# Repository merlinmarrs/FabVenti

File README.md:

# FabVenti
Stepper Motor Driver with Atmega328p and DRV8833
Developed by Fab Lab Digiscope

See PDF for assembly instructions

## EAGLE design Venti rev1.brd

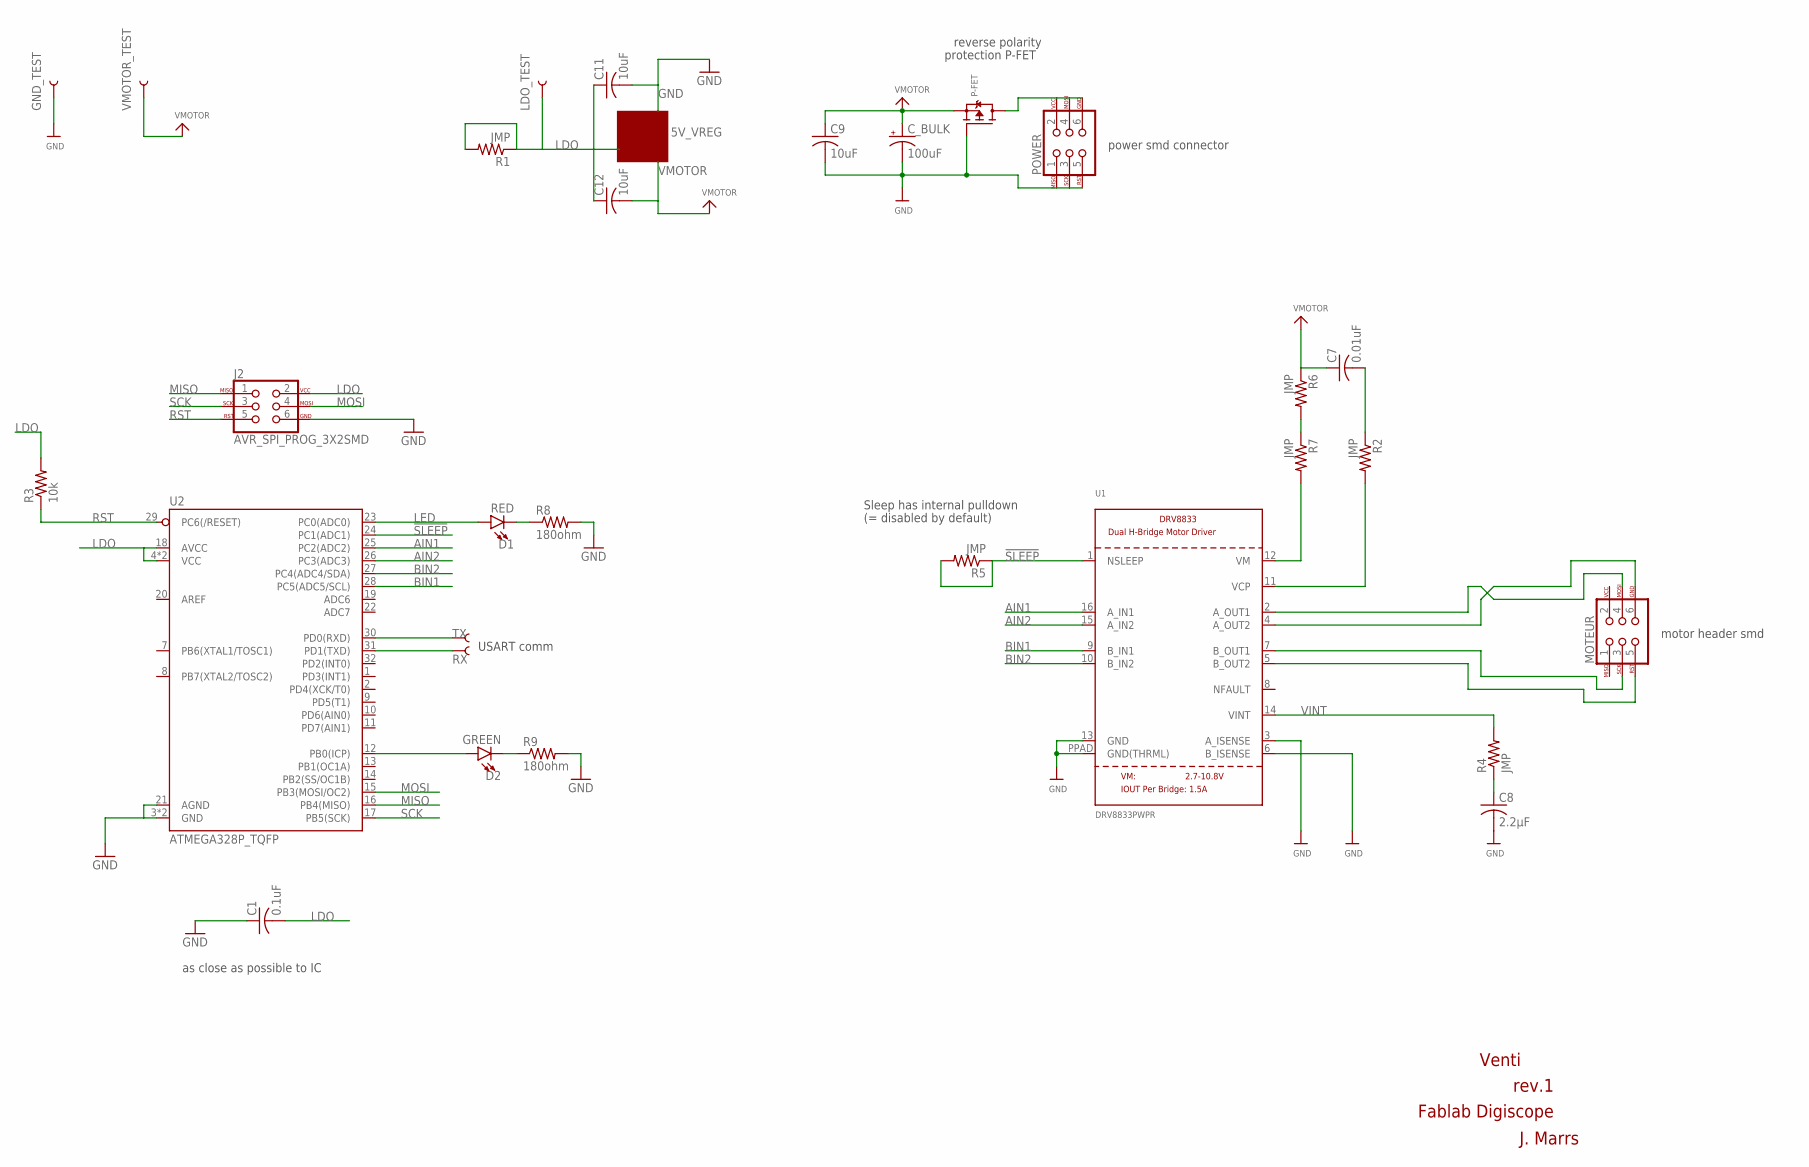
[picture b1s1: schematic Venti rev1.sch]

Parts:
5V_VREG: MOSFET_PCH-DMG2305UX-7; SOT23-3
C1: 0.1uF; C1206
C7: 0.01uF; C1206
C8: 2.2μF; C1206
C9, C11, C12: 10uF; C1206
C_BULK: 100uF; CPOL-RADIAL-2.5MM-6.5MM
D1: RED; LED-1206
D2: GREEN; LED-1206
GND_TEST: TEST-POINT3; PAD.03X.03
J2: AVR_SPI_PROG_3X2SMD; 2X3_SMT_POSTS
LDO_TEST: TEST-POINT3; PAD.03X.03
MOTEUR: AVR_SPI_PROG_3X2SMD; 2X3_SMT_POSTS
P-FET: MOSFET-PWIDE; SOT23-WIDE
POWER: AVR_SPI_PROG_3X2SMD; 2X3_SMT_POSTS
R1, R2, R4, R5, R6, R7: JMP; R1206
R3: 10k; R1206
R8, R9: 180ohm; R1206
RX: TEST-POINT3; PAD.03X.03
TX: TEST-POINT3; PAD.03X.03
U1: DRV8833PWPR; HTSSOP16
U2: ATMEGA328P_TQFP; TQFP32-08
VMOTOR_TEST: TEST-POINT3; PAD.03X.03

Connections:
!SLEEP: R5.1, R5.2, U1.1 (NSLEEP), U2.24 (PC1(ADC1))
AIN1: U1.16 (A_IN1), U2.25 (PC2(ADC2))
AIN2: U1.15 (A_IN2), U2.26 (PC3(ADC3))
AOUT1: MOTEUR.4, U1.2 (A_OUT1)
AOUT2: MOTEUR.6, U1.4 (A_OUT2)
BIN1: U1.9 (B_IN1), U2.28 (PC5(ADC5/SCL))
BIN2: U1.10 (B_IN2), U2.27 (PC4(ADC4/SDA))
BOUT1: MOTEUR.3, U1.7 (B_OUT1)
BOUT2: MOTEUR.5, U1.5 (B_OUT2)
GND: 5V_VREG.3 (D), C1.1, C8.2, C9.2, C11.2, C_BULK.2 (-), GND_TEST.P$1, J2.6, P-FET.1 (G), POWER.1, POWER.3, POWER.5, R8.2, R9.2, U1.3 (A_ISENSE), U1.6 (B_ISENSE), U1.13 (GND), U1.PPAD (GND(THRML)), U2.3 (GND), U2.5 (GND), U2.21 (AGND)
LDO: 5V_VREG.1 (G), C1.2, C11.1, C12.1, J2.2, LDO_TEST.P$1, R1.1, R1.2, R3.2, U2.4 (VCC), U2.6 (VCC), U2.18 (AVCC)
LED: D1.A, U2.23 (PC0(ADC0))
MISO: J2.1, U2.16 (PB4(MISO))
MOSI: J2.4, U2.15 (PB3(MOSI/OC2))
unnamed: C8.1, R4.1
unnamed: C7.2, R2.1
unnamed: R7.2, U1.12 (VM)
unnamed: R6.2, R7.1
unnamed: TX.P$1, U2.30 (PD0(RXD))
unnamed: RX.P$1, U2.31 (PD1(TXD))
unnamed: R2.2, U1.11 (VCP)
unnamed: D2.A, U2.12 (PB0(ICP))
unnamed: D1.C, R8.1
unnamed: D2.C, R9.1
PWRIN: P-FET.3 (D), POWER.2, POWER.4, POWER.6
RST: J2.5, R3.1, U2.29 (PC6(/RESET))
SCK: J2.3, U2.17 (PB5(SCK))
VINT: R4.2, U1.14 (VINT)
VMOTOR: 5V_VREG.2 (S), C7.1, C9.1, C12.2, C_BULK.1 (+), P-FET.2 (S), R6.1, VMOTOR_TEST.P$1

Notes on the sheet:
Sleep has internal pulldown
(= disabled by default)
motor header smd
power smd connector
Venti
rev.1
Fablab Digiscope
J. Marrs
USART comm
as close as possible to IC
reverse polarity
protection P-FET

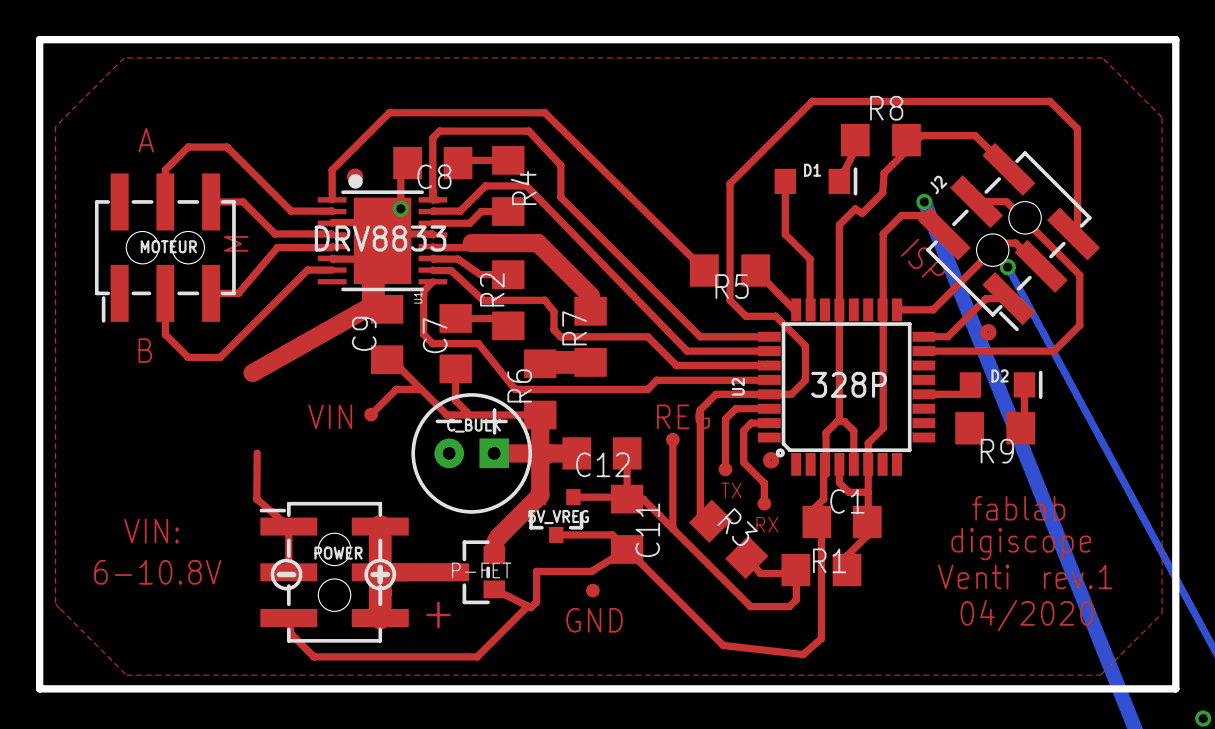
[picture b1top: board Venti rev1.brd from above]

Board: 2 copper layers, 63.1 x 36.1 mm, 33 parts (1 on the bottom side), 29 nets.

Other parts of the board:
U$15: SYMBOL_PLUS
U$16: SYMBOL_MINUS
U$17: ADAFRUIT_3.5MM

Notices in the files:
parts and their libraries:
SparkFun-IC-Microcontroller: Licensing: Creative Commons ShareAlike 4.0 International - https://creativecommons.org/licenses/by-sa/4.0
